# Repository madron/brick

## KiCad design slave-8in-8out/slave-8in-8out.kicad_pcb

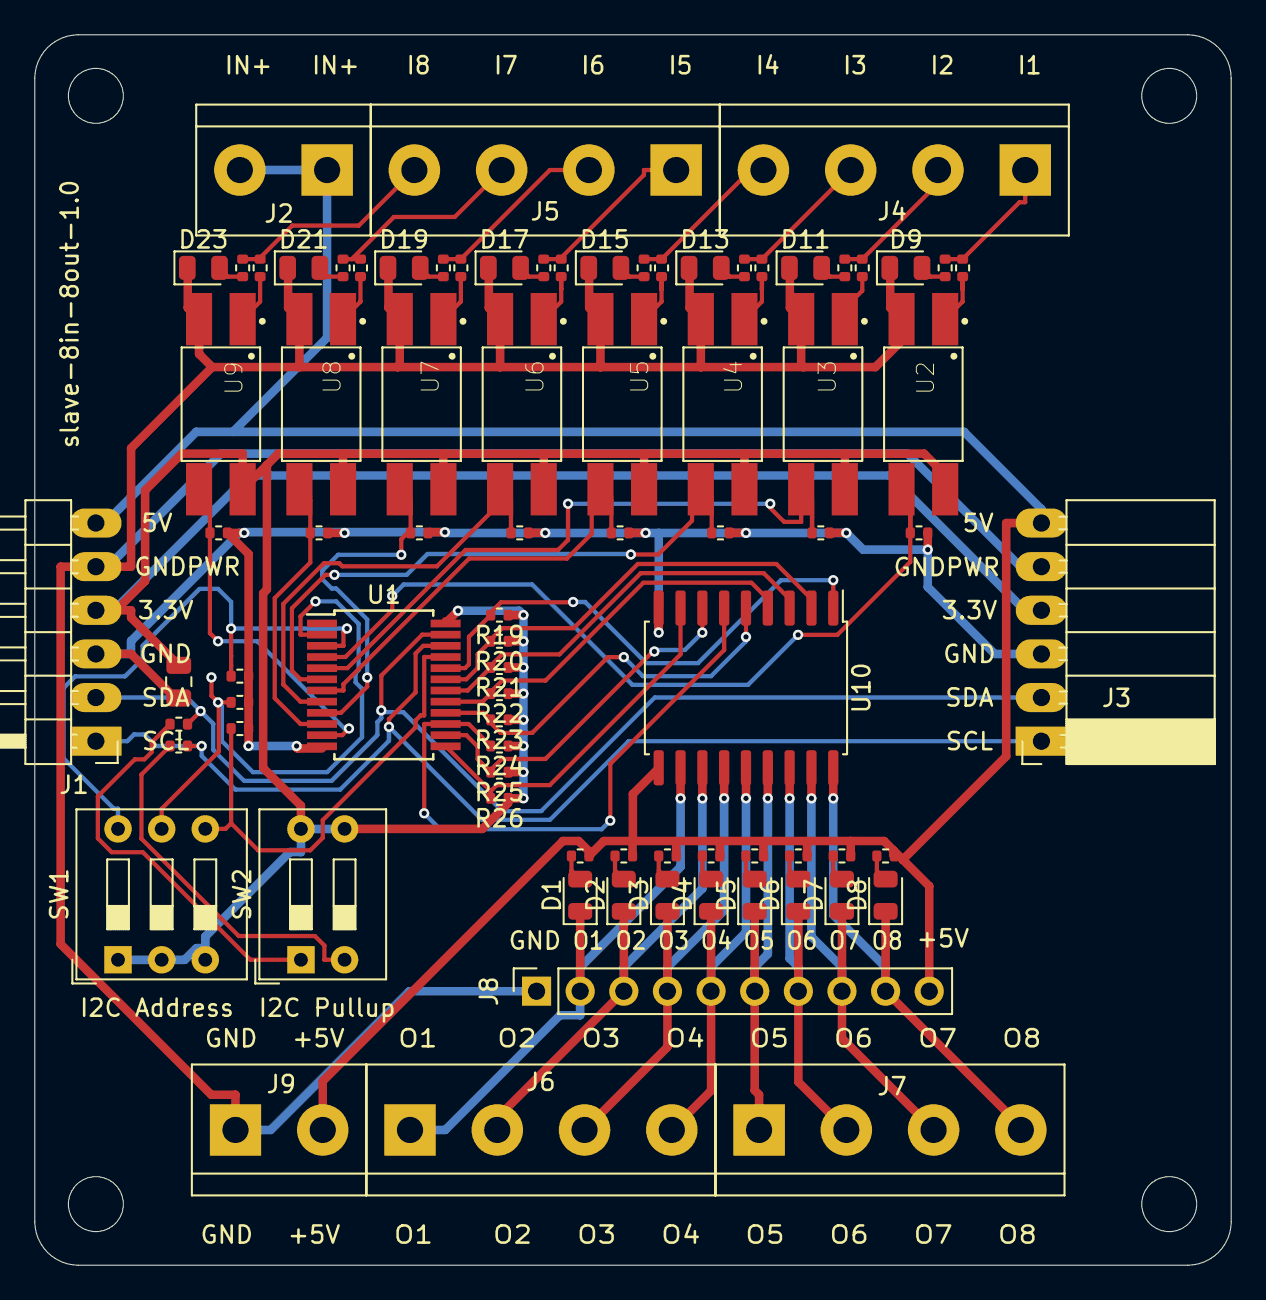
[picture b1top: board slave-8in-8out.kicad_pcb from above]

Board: 2 copper layers, 69.6 x 71.6 mm, 87 parts (0 on the bottom side), 67 nets.

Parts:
C1: 100nF; C_0805_2012Metric
D1, D2, D3, D4, D5, D6, D7, D8, D9, D11, D13, D15, D17, D19, D21, D23: LED; LED_0805_2012Metric
H1, H2, H3, H4: MountingHole; MountingHole_3.2mm_M3
J1: Conn_01x06_Male; PinHeader_1x06_P2.54mm_Horizontal
J2, J9: Screw_Terminal_01x02; TerminalBlock_bornier-2_P5.08mm
J3: Conn_01x06_Female; PinSocket_1x06_P2.54mm_Horizontal
J4, J5, J6, J7: Screw_Terminal_01x04; TerminalBlock_bornier-4_P5.08mm
J8: Conn_01x10_Female; PinSocket_1x10_P2.54mm_Vertical
R1, R2, R5, R8, R19, R20, R21, R22, R23, R24, R25, R26, R28, R29, R30, R31, R34, R37, R40, R43, R46: 10k; R_0402_1005Metric
R3, R4, R6, R7, R9, R10, R11, R12, R13, R14, R15, R16, R17, R18, R32, R33, R35, R36, R38, R39, R41, R42, R44, R45: 680; R_0402_1005Metric
SW1: SW_DIP_x03; SW_DIP_SPSTx03_Slide_9.78x9.8mm_W7.62mm_P2.54mm
SW2: SW_DIP_x02; SW_DIP_SPSTx02_Slide_9.78x7.26mm_W7.62mm_P2.54mm
U1: PCF8575; SSOP-24_5.3x8.2mm_P0.65mm
U2, U3, U4, U5, U6, U7, U8, U9: EL817
U10: ULN2803A; SOIC-18W_7.5x11.6mm_P1.27mm

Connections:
+3V3: C1.1, J1.4, J3.4, R19.1, R20.1, R21.1, R22.1, R23.1, R24.1, R25.1, R26.1, SW1.1, SW1.2, SW1.3, SW2.3, SW2.4, U1.24 (VCC), U2.4, U3.4, U4.4, U5.4, U6.4, U7.4, U8.4, U9.4
+5V: J1.6, J2.1, J2.2, J3.6, J8.10, J9.2, R11.2, R12.2, R13.2, R14.2, R15.2, R16.2, R17.2, R18.2, U10.10 (COM)
A0: R30.1, SW1.4, U1.21 (A0)
A1: R29.1, SW1.5, U1.2 (A1)
A2: R28.1, SW1.6, U1.3 (A2)
GND: C1.2, J1.3, J3.3, R5.1, R8.1, R28.2, R29.2, R30.2, R31.1, R34.1, R37.1, R40.1, R43.1, R46.1, U1.12 (GND), U10.9 (GND)
GNDPWR: D9.1 (K), D11.1 (K), D13.1 (K), D15.1 (K), D17.1 (K), D19.1 (K), D21.1 (K), D23.1 (K), J1.5, J3.5, J8.1, J9.1, U2.2, U3.2, U4.2, U5.2, U6.2, U7.2, U8.2, U9.2
GPA0: R26.2, U1.13 (P10), U10.8 (I8)
GPA1: R25.2, U1.14 (P11), U10.7 (I7)
GPA2: R24.2, U1.15 (P12), U10.6 (I6)
GPA3: R23.2, U1.16 (P13), U10.5 (I5)
GPA4: R22.2, U1.17 (P14), U10.4 (I4)
GPA5: R21.2, U1.18 (P15), U10.3 (I3)
GPA6: R20.2, U1.19 (P16), U10.2 (I2)
GPA7: R19.2, U1.20 (P17), U10.1 (I1)
GPB0: R5.2, U1.4 (P00), U2.3
GPB1: R8.2, U1.5 (P01), U3.3
GPB2: R31.2, U1.6 (P02), U4.3
GPB3: R34.2, U1.7 (P03), U5.3
GPB4: R37.2, U1.8 (P04), U6.3
GPB5: R40.2, U1.9 (P05), U7.3
GPB6: R43.2, U1.10 (P06), U8.3
GPB7: R46.2, U1.11 (P07), U9.3
I1: J4.1, R3.1, R4.2
I2: J4.2, R6.1, R7.2
I3: J4.3, R9.1, R10.2
I4: J4.4, R32.1, R33.2
I5: J5.1, R35.1, R36.2
I6: J5.2, R38.1, R39.2
I7: J5.3, R41.1, R42.2
I8: J5.4, R44.1, R45.2
unnamed: D1.2 (A), R12.1
unnamed: D2.2 (A), R13.1
unnamed: D3.2 (A), R14.1
unnamed: D4.2 (A), R15.1
unnamed: D5.2 (A), R16.1
unnamed: D6.2 (A), R17.1
unnamed: D7.2 (A), R18.1
unnamed: D8.2 (A), R11.1
unnamed: D9.2 (A), R3.2
unnamed: D11.2 (A), R6.2
unnamed: D13.2 (A), R9.2
unnamed: D15.2 (A), R32.2
unnamed: D17.2 (A), R35.2
unnamed: D19.2 (A), R38.2
unnamed: D21.2 (A), R41.2
unnamed: D23.2 (A), R44.2
unnamed: R1.1, SW2.1
unnamed: R2.1, SW2.2
unnamed: R4.1, U2.1
unnamed: R7.1, U3.1
unnamed: R10.1, U4.1
unnamed: R33.1, U5.1
unnamed: R36.1, U6.1
unnamed: R39.1, U7.1
unnamed: R42.1, U8.1
unnamed: R45.1, U9.1
O1: D1.1 (K), J6.1, J8.2, U10.11 (O8)
O2: D2.1 (K), J6.2, J8.3, U10.12 (O7)
O3: D3.1 (K), J6.3, J8.4, U10.13 (O6)
O4: D4.1 (K), J6.4, J8.5, U10.14 (O5)
O5: D5.1 (K), J7.1, J8.6, U10.15 (O4)
O6: D6.1 (K), J7.2, J8.7, U10.16 (O3)
O7: D7.1 (K), J7.3, J8.8, U10.17 (O2)
O8: D8.1 (K), J7.4, J8.9, U10.18 (O1)
SCL: J1.1, J3.1, R2.2, U1.22 (SCL)
SDA: J1.2, J3.2, R1.2, U1.23 (SDA)

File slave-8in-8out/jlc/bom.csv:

Comment,Designator,Footprint,LCSC Part #
100nF Unpolarized capacitor,C1,C_0805_2012Metric,C49678
LED Light emitting diode,"D1,D2,D3,D4,D5,D6,D7,D8,D9,D11,D13,D15,D17,D19,D21,D23",LED_0805_2012Metric,C84256
10k Resistor,"R1,R2,R5,R8,R19,R20,R21,R22,R23,R24,R25,R26,R28,R29,R30,R31,R34,R37,R40,R43,R46",R_0402_1005Metric,C25744
680 Resistor,"R3,R4,R6,R7,R9,R10,R11,R12,R13,R14,R15,R16,R17,R18,R32,R33,R35,R36,R38,R39,R41,R42,R44,R45",R_0402_1005Metric,C25130
PCF8575 ,U1,SSOP-24_5.3x8.2mm_P0.65mm,C12251
"EL817 DC Optocoupler, Vce 35V, CTR 50-300%, DIP-4","U2,U3,U4,U5,U6,U7,U8,U9",EL817,C106900
"ULN2803A Darlington Transistor Arrays, SOIC18/DIP18",U10,SOIC-18W_7.5x11.6mm_P1.27mm,C9683

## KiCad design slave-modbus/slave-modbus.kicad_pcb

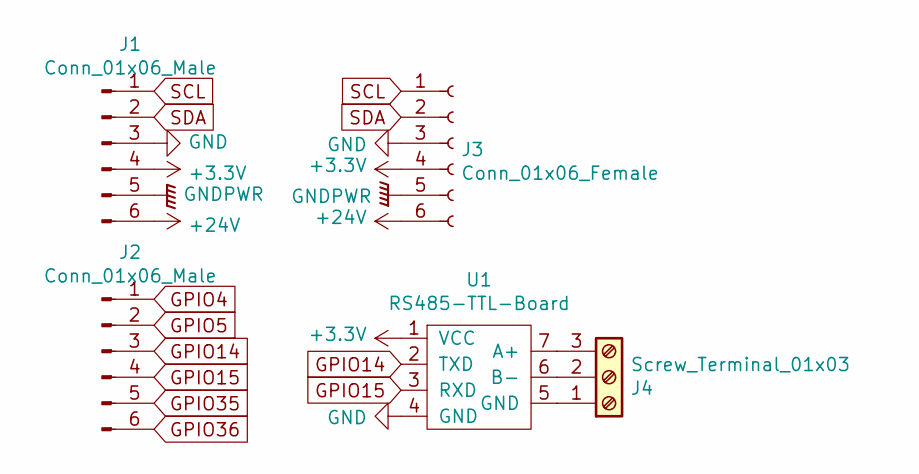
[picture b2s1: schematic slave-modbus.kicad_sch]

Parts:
J1, J2: Conn_01x06_Male; PinHeader_1x06_P2.54mm_Horizontal
J3: Conn_01x06_Female; PinSocket_1x06_P2.54mm_Horizontal
J4: Screw_Terminal_01x03; TerminalBlock_Phoenix_PT-1,5-3-3.5-H_1x03_P3.50mm_Horizontal
U1: RS485-TTL-Board; RS485-TTL-Board-DsdTech

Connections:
+3V3: J1.4, J3.4, U1.1 (VCC)
+24V: J1.6, J3.6
GND: J1.3, J3.3, U1.4 (GND)
GNDPWR: J1.5, J3.5
GPIO4: J2.1
GPIO5: J2.2
GPIO14: J2.3, U1.2 (TXD)
GPIO15: J2.4, U1.3 (RXD)
GPIO35: J2.5
GPIO36: J2.6
unnamed: J4.1, U1.5 (GND)
unnamed: J4.2, U1.6 (B-)
unnamed: J4.3, U1.7 (A+)
SCL: J1.1, J3.1
SDA: J1.2, J3.2

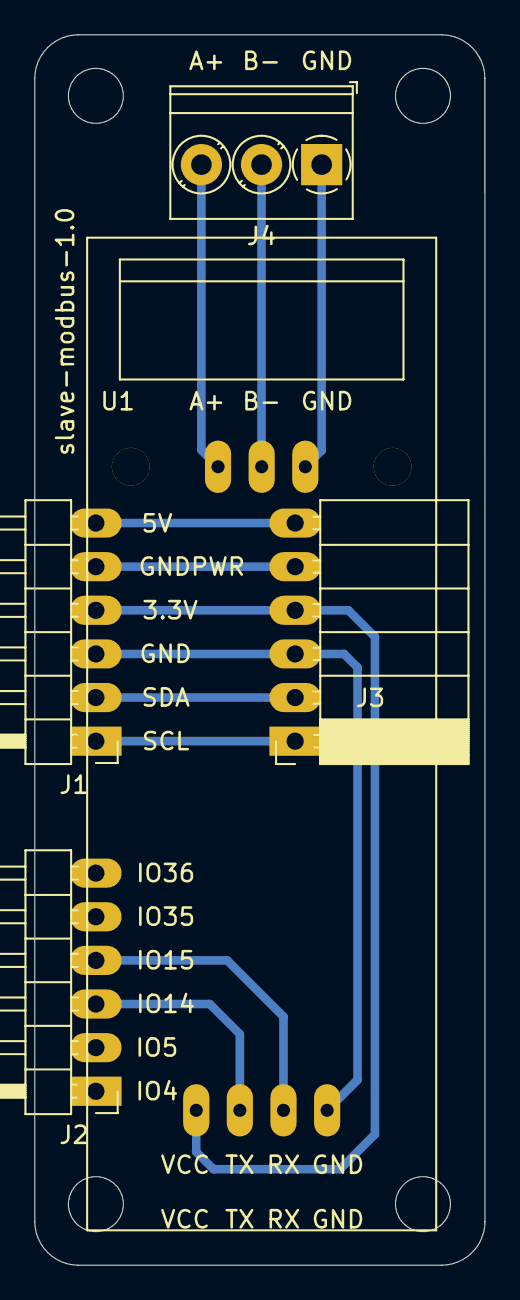
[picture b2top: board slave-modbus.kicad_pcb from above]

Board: 2 copper layers, 26.2 x 71.6 mm, 9 parts (0 on the bottom side), 11 nets.

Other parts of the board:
H1, H2, H3, H4: MountingHole; MountingHole_3.2mm_M3

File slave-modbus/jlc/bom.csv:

Comment,Designator,Footprint,LCSC Part #
"Conn_01x06_Male Generic connector, single row, 01x06, script generated (kicad-library-utils/schlib/autogen/connector/)","J1,J2",PinHeader_1x06_P2.54mm_Horizontal,
"Conn_01x06_Female Generic connector, single row, 01x06, script generated (kicad-library-utils/schlib/autogen/connector/)",J3,PinSocket_1x06_P2.54mm_Horizontal,
"Screw_Terminal_01x03 Generic screw terminal, single row, 01x03, script generated (kicad-library-utils/schlib/autogen/connector/)",J4,"TerminalBlock_Phoenix_PT-1,5-3-3.5-H_1x03_P3.50mm_Horizontal",
RS485-TTL-Board ,U1,RS485-TTL-Board-DsdTech,

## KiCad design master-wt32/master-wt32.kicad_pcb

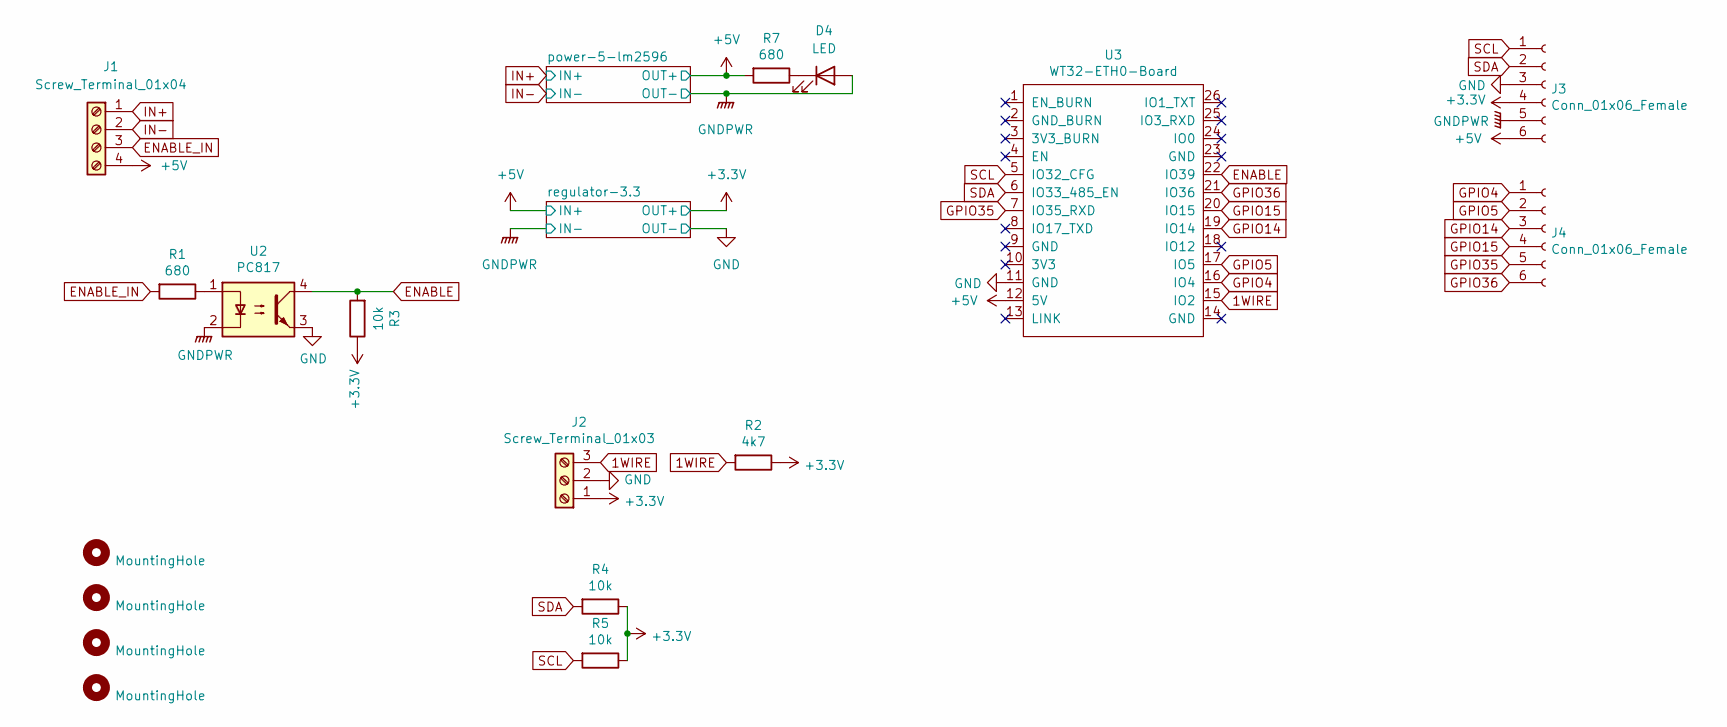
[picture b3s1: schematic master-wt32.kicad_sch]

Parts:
D4: LED; LED_D5.0mm
H1, H2, H3, H4: MountingHole; MountingHole_3.2mm_M3
J1: Screw_Terminal_01x04; TerminalBlock_bornier-4_P5.08mm
J2: Screw_Terminal_01x03; TerminalBlock_bornier-3_P5.08mm
J3, J4: Conn_01x06_Female; PinSocket_1x06_P2.54mm_Horizontal
R1, R7: 680; R_Axial_DIN0207_L6.3mm_D2.5mm_P7.62mm_Horizontal
R2: 4k7; R_Axial_DIN0207_L6.3mm_D2.5mm_P7.62mm_Horizontal
R3: 10k; R_Axial_DIN0207_L6.3mm_D2.5mm_P7.62mm_Horizontal
R4, R5: 10k; R_Axial_DIN0207_L6.3mm_D2.5mm_P7.62mm_Horizontal; LCSC C25744
U2: PC817; DIP-4_W7.62mm
U3: WT32-ETH0-Board; WT32-ETH01-Board-Reversed

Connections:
1WIRE: J2.3, R2.2, U3.15 (IO2)
+3V3: J2.1, J3.4, R2.1, R3.1, R4.1, R5.1; also elsewhere on the board
+5V: J1.4, J3.6, R7.2, U3.12 (5V); also elsewhere on the board
ENABLE: R3.2, U2.4, U3.22 (IO39)
ENABLE_IN: J1.3, R1.2
GNDPWR: D4.2 (A), J2.2, J3.3, J3.5, U2.2, U2.3, U3.11 (GND); also elsewhere on the board
GPIO4: J4.1, U3.16 (IO4)
GPIO5: J4.2, U3.17 (IO5)
GPIO14: J4.3, U3.19 (IO14)
GPIO15: J4.4, U3.20 (IO15)
GPIO35: J4.5, U3.7 (IO35_RXD)
GPIO36: J4.6, U3.21 (IO36)
IN+: J1.1; also elsewhere on the board
IN-: J1.2; also elsewhere on the board
unnamed: D4.1 (K), R7.1
unnamed: R1.1, U2.1
SCL: J3.1, R5.2, U3.5 (IO32_CFG)
SDA: J3.2, R4.2, U3.6 (IO33_485_EN)

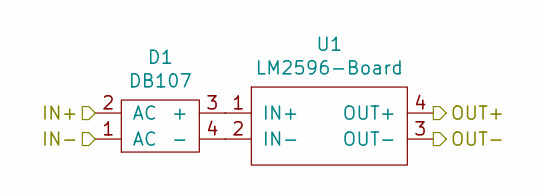
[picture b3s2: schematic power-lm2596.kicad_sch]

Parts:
D1: DB107
U1: LM2596-Board

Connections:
+5V: U1.4 (OUT+); also elsewhere on the board
GNDPWR: U1.3 (OUT-); also elsewhere on the board
IN+: D1.2 (AC); also elsewhere on the board
IN-: D1.1 (AC); also elsewhere on the board
unnamed: D1.3 (+), U1.1 (IN+)
unnamed: D1.4 (-), U1.2 (IN-)

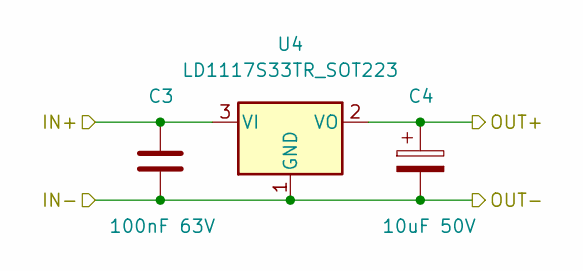
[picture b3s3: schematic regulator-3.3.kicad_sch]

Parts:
C3: 100nF 63V; C_Rect_L7.0mm_W2.0mm_P5.00mm
C4: 10uF 50V; CP_Radial_D5.0mm_P2.50mm
U4: LD1117S33TR_SOT223; TO-220-3_Vertical

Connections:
+3V3: C4.1, U4.2 (VO); also elsewhere on the board
+5V: C3.1, U4.3 (VI); also elsewhere on the board
GNDPWR: C3.2, C4.2, U4.1 (GND); also elsewhere on the board

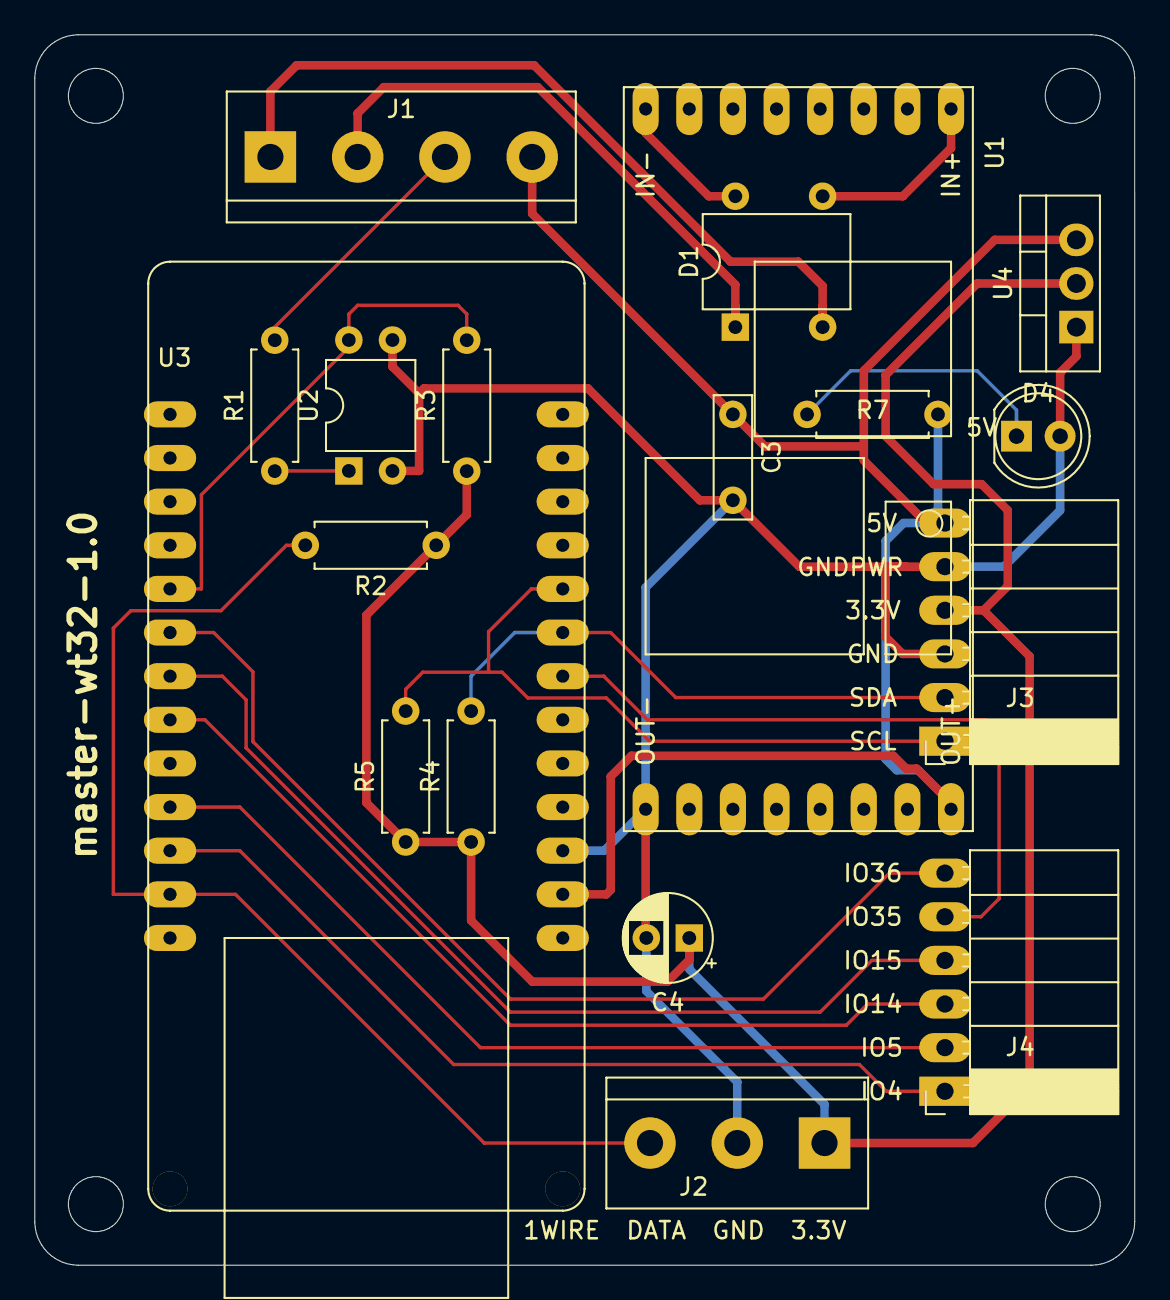
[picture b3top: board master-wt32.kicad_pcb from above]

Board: 2 copper layers, 64.0 x 71.6 mm, 22 parts (0 on the bottom side), 20 nets.

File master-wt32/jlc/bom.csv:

Comment,Designator,Footprint,LCSC Part #
100nF 63V Unpolarized capacitor,C3,C_Rect_L7.0mm_W2.0mm_P5.00mm,
10uF 50V Polarized capacitor,C4,CP_Radial_D5.0mm_P2.50mm,
DB107 ,D1,DB107,
LED Light emitting diode,D4,LED_D5.0mm,
MountingHole Mounting Hole without connection,"H1,H2,H3,H4",MountingHole_3.2mm_M3,
"Screw_Terminal_01x04 Generic screw terminal, single row, 01x04, script generated (kicad-library-utils/schlib/autogen/connector/)",J1,TerminalBlock_bornier-4_P5.08mm,
"Screw_Terminal_01x03 Generic screw terminal, single row, 01x03, script generated (kicad-library-utils/schlib/autogen/connector/)",J2,TerminalBlock_bornier-3_P5.08mm,
"Conn_01x06_Female Generic connector, single row, 01x06, script generated (kicad-library-utils/schlib/autogen/connector/)","J3,J4",PinSocket_1x06_P2.54mm_Horizontal,
680 Resistor,"R1,R7",R_Axial_DIN0207_L6.3mm_D2.5mm_P7.62mm_Horizontal,
4k7 Resistor,R2,R_Axial_DIN0207_L6.3mm_D2.5mm_P7.62mm_Horizontal,
10k Resistor,"R3,R4,R5",R_Axial_DIN0207_L6.3mm_D2.5mm_P7.62mm_Horizontal,C25744
LM2596-Board ,U1,LM2596-Board,
"PC817 DC Optocoupler, Vce 35V, CTR 50-300%, DIP-4",U2,DIP-4_W7.62mm,
WT32-ETH0-Board ,U3,WT32-ETH01-Board-Reversed,
"LD1117S33TR_SOT223 800mA Fixed Low Drop Positive Voltage Regulator, Fixed Output 3.3V, SOT-223",U4,TO-220-3_Vertical,

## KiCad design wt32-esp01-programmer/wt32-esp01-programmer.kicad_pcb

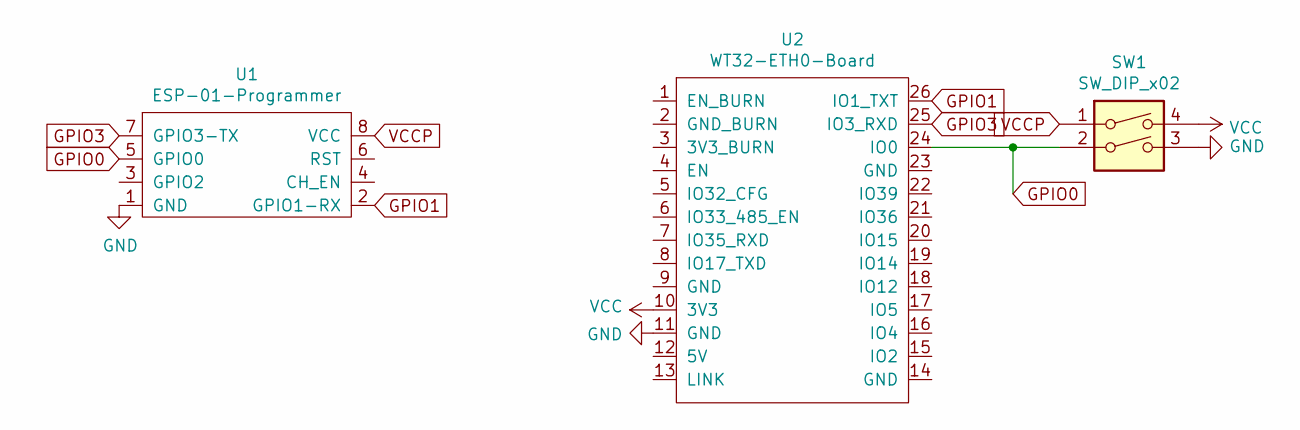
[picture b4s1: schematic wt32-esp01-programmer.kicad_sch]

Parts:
SW1: SW_DIP_x02; SW_DIP_SPSTx02_Slide_9.78x7.26mm_W7.62mm_P2.54mm
U1: ESP-01-Programmer
U2: WT32-ETH0-Board; WT32-ETH01-Board-Reversed

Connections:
GND: SW1.3, U1.1 (GND), U2.11 (GND)
GPIO0: SW1.2, U1.5 (GPIO0), U2.24 (IO0)
GPIO1: U1.2 (GPIO1-RX), U2.26 (IO1_TXT)
GPIO3: U1.7 (GPIO3-TX), U2.25 (IO3_RXD)
VCC: SW1.4, U2.10 (3V3)
VCCP: SW1.1, U1.8 (VCC)

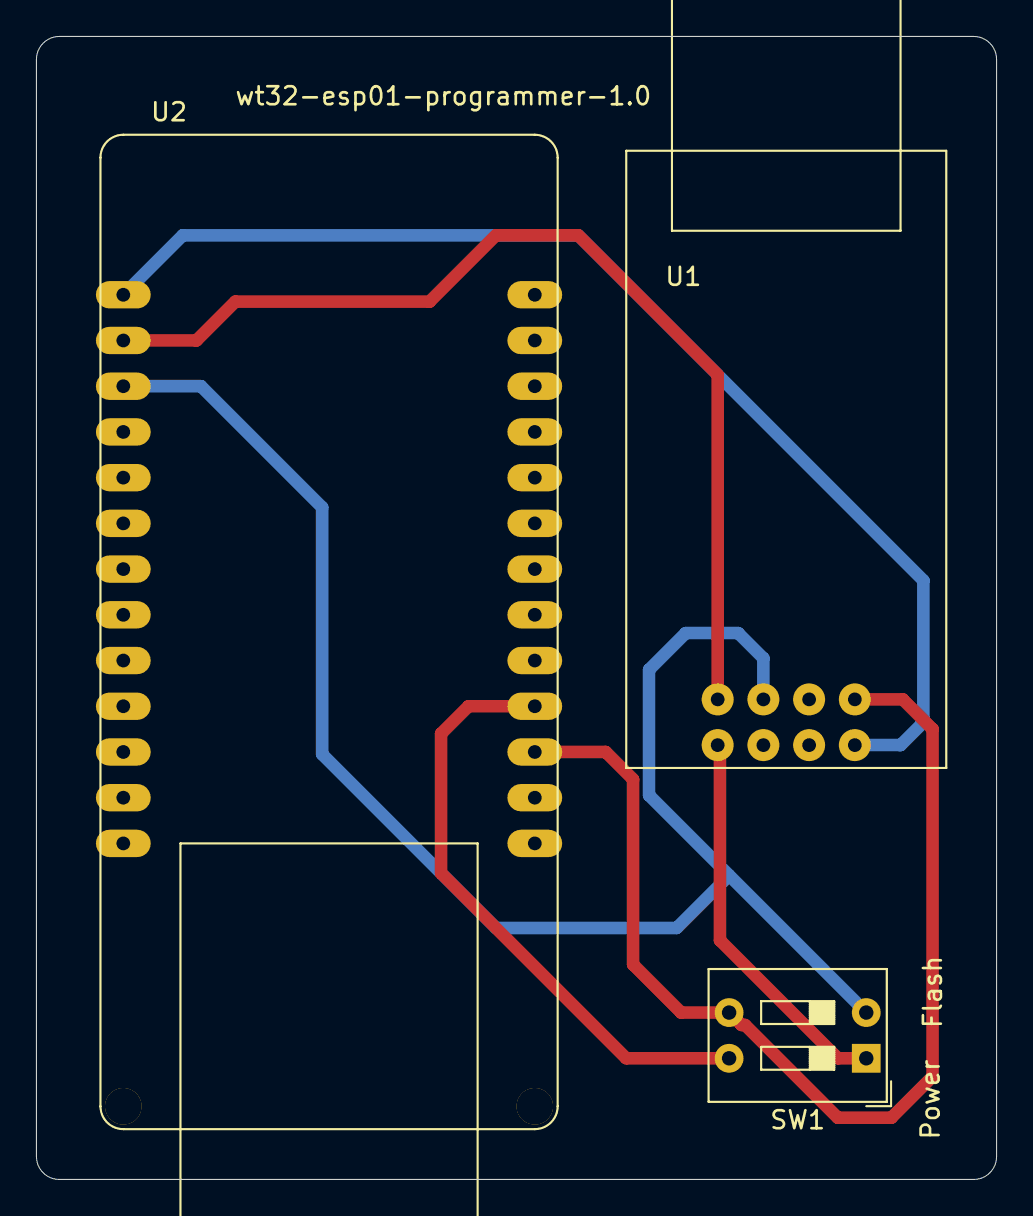
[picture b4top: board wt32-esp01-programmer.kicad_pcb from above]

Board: 2 copper layers, 53.3 x 63.5 mm, 3 parts (0 on the bottom side), 6 nets.

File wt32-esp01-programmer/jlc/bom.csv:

Comment,Designator,Footprint,LCSC Part #
"SW_DIP_x02 2x DIP Switch, Single Pole Single Throw (SPST) switch, small symbol",SW1,SW_DIP_SPSTx02_Slide_9.78x7.26mm_W7.62mm_P2.54mm,
ESP-01-Programmer ,U1,ESP-01-Programmer,
WT32-ETH0-Board ,U2,WT32-ETH01-Board-Reversed,

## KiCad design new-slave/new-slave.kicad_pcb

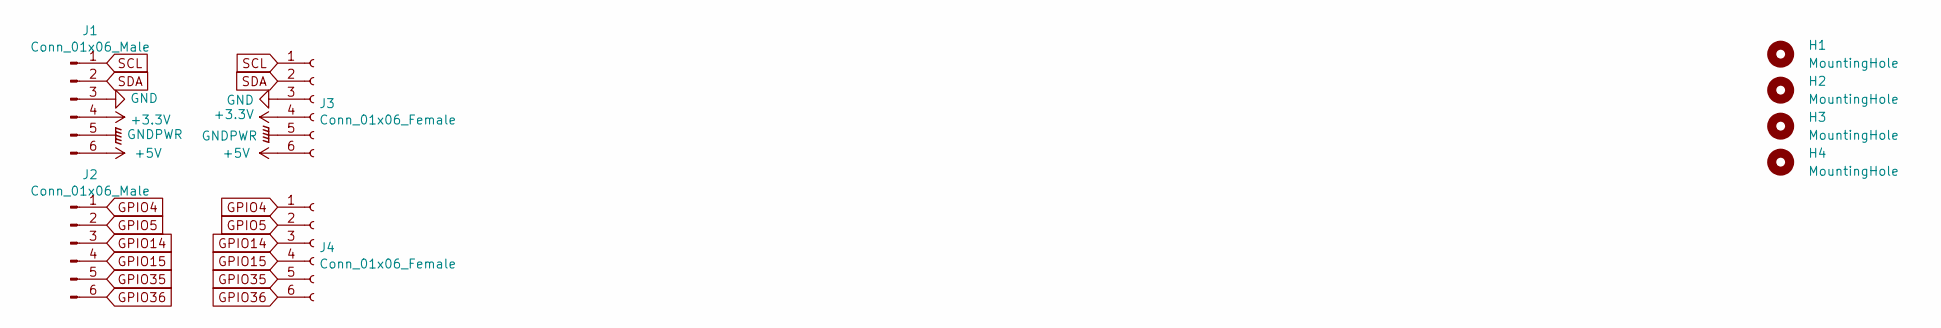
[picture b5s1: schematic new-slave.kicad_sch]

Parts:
H1, H2, H3, H4: MountingHole; MountingHole_3.2mm_M3
J1, J2: Conn_01x06_Male; PinHeader_1x06_P2.54mm_Horizontal
J3, J4: Conn_01x06_Female; PinSocket_1x06_P2.54mm_Horizontal

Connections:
+3V3: J1.4, J3.4
+5V: J1.6, J3.6
GND: J1.3, J3.3
GNDPWR: J1.5, J3.5
GPIO4: J2.1, J4.1
GPIO5: J2.2, J4.2
GPIO14: J2.3, J4.3
GPIO15: J2.4, J4.4
GPIO35: J2.5, J4.5
GPIO36: J2.6, J4.6
SCL: J1.1, J3.1
SDA: J1.2, J3.2

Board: 2 copper layers, 8 parts (0 on the bottom side), 12 nets, no tracks yet.

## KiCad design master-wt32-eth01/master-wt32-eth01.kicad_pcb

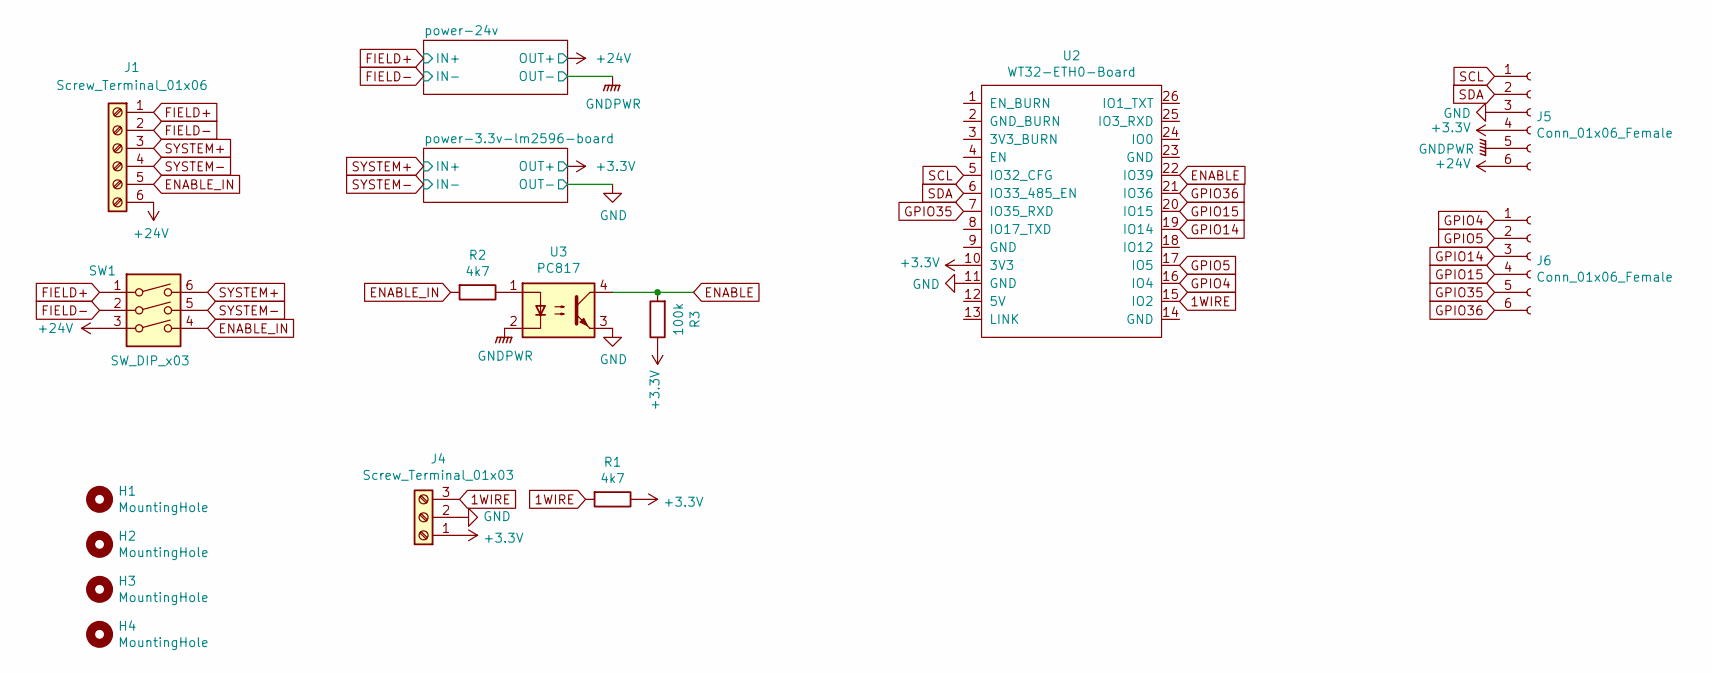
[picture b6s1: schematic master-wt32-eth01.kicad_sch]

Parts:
H1, H2, H3, H4: MountingHole; MountingHole_3.2mm_M3
J1: Screw_Terminal_01x06; TerminalBlock_bornier-6_P5.08mm
J4: Screw_Terminal_01x03; TerminalBlock_bornier-3_P5.08mm
J5, J6: Conn_01x06_Female; PinSocket_1x06_P2.54mm_Horizontal
R1, R2: 4k7; R_Axial_DIN0207_L6.3mm_D2.5mm_P7.62mm_Horizontal
R3: 100k; R_Axial_DIN0207_L6.3mm_D2.5mm_P7.62mm_Horizontal
SW1: SW_DIP_x03; SW_DIP_SPSTx03_Slide_9.78x9.8mm_W7.62mm_P2.54mm
U2: WT32-ETH0-Board; WT32-ETH01-Board-Reversed
U3: PC817; DIP-4_W7.62mm

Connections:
1WIRE: J4.3, R1.2, U2.15 (IO2)
+3V3: J4.1, J5.4, R1.1, R3.1, U2.10 (3V3); also elsewhere on the board
+24V: J1.6, J5.6, SW1.3; also elsewhere on the board
ENABLE: R3.2, U2.22 (IO39), U3.4
ENABLE_IN: J1.5, R2.2, SW1.4
FIELD+: J1.1, SW1.1; also elsewhere on the board
FIELD-: J1.2, SW1.2; also elsewhere on the board
GND: J4.2, J5.3, U2.11 (GND), U3.3; also elsewhere on the board
GNDPWR: J5.5, U3.2; also elsewhere on the board
GPIO4: J6.1, U2.16 (IO4)
GPIO5: J6.2, U2.17 (IO5)
GPIO14: J6.3, U2.19 (IO14)
GPIO15: J6.4, U2.20 (IO15)
GPIO35: J6.5, U2.7 (IO35_RXD)
GPIO36: J6.6, U2.21 (IO36)
unnamed: R2.1, U3.1
SCL: J5.1, U2.5 (IO32_CFG)
SDA: J5.2, U2.6 (IO33_485_EN)
SYSTEM+: J1.3, SW1.6; also elsewhere on the board
SYSTEM-: J1.4, SW1.5; also elsewhere on the board

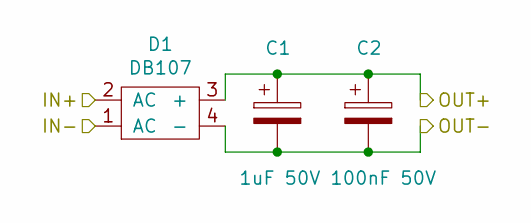
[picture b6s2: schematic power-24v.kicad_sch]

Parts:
C1: 1uF 50V; CP_Radial_D5.0mm_P2.50mm
C2: 100nF 50V; C_Rect_L7.0mm_W2.0mm_P5.00mm
D1: DB107

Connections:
+24V: C1.1, C2.1, D1.3 (+); also elsewhere on the board
FIELD+: D1.2 (AC); also elsewhere on the board
FIELD-: D1.1 (AC); also elsewhere on the board
GNDPWR: C1.2, C2.2, D1.4 (-); also elsewhere on the board

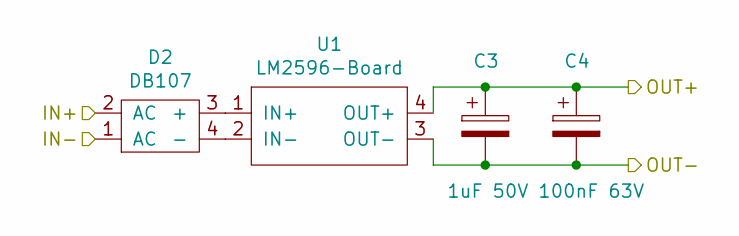
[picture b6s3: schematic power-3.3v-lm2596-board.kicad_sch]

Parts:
C3: 1uF 50V; CP_Radial_D5.0mm_P2.50mm
C4: 100nF 63V; C_Rect_L7.0mm_W2.0mm_P5.00mm
D2: DB107
U1: LM2596-Board

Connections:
+3V3: C3.1, C4.1, U1.4 (OUT+); also elsewhere on the board
GND: C3.2, C4.2, U1.3 (OUT-); also elsewhere on the board
unnamed: D2.3 (+), U1.1 (IN+)
unnamed: D2.4 (-), U1.2 (IN-)
SYSTEM+: D2.2 (AC); also elsewhere on the board
SYSTEM-: D2.1 (AC); also elsewhere on the board

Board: 2 copper layers, 21 parts (0 on the bottom side), 22 nets, no tracks yet.

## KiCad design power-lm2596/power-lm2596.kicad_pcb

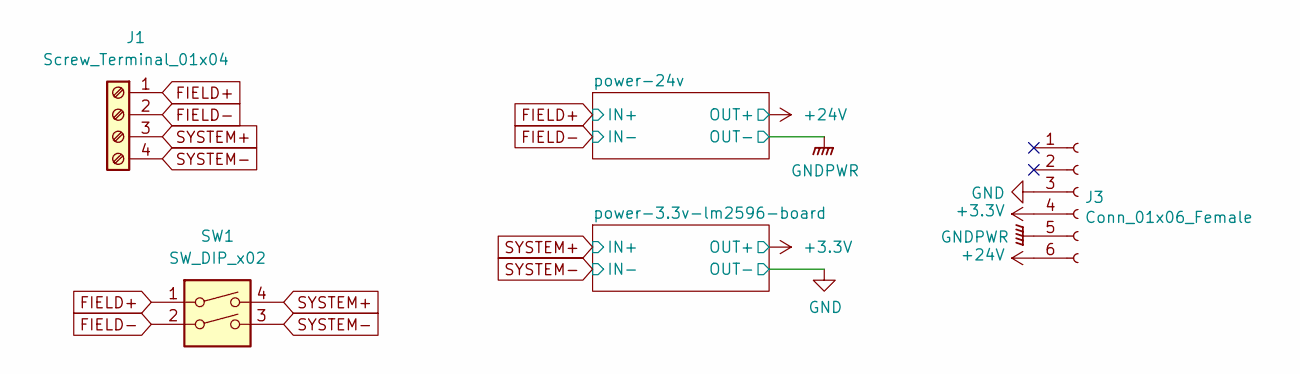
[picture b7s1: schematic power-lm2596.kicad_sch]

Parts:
J1: Screw_Terminal_01x04; TerminalBlock_bornier-4_P5.08mm
J3: Conn_01x06_Female; PinSocket_1x06_P2.54mm_Horizontal
SW1: SW_DIP_x02; SW_DIP_SPSTx02_Slide_9.78x7.26mm_W7.62mm_P2.54mm

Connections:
+3V3: J3.4; also elsewhere on the board
+24V: J3.6; also elsewhere on the board
FIELD+: J1.1, SW1.1; also elsewhere on the board
FIELD-: J1.2, SW1.2; also elsewhere on the board
GND: J3.3; also elsewhere on the board
GNDPWR: J3.5; also elsewhere on the board
SYSTEM+: J1.3, SW1.4; also elsewhere on the board
SYSTEM-: J1.4, SW1.3; also elsewhere on the board

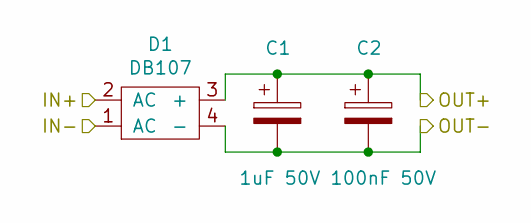
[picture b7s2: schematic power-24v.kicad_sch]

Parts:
C1: 1uF 50V; CP_Radial_D5.0mm_P2.50mm
C2: 100nF 50V; C_Rect_L7.0mm_W2.0mm_P5.00mm
D1: DB107

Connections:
+24V: C1.1, C2.1, D1.3 (+); also elsewhere on the board
FIELD+: D1.2 (AC); also elsewhere on the board
FIELD-: D1.1 (AC); also elsewhere on the board
GNDPWR: C1.2, C2.2, D1.4 (-); also elsewhere on the board

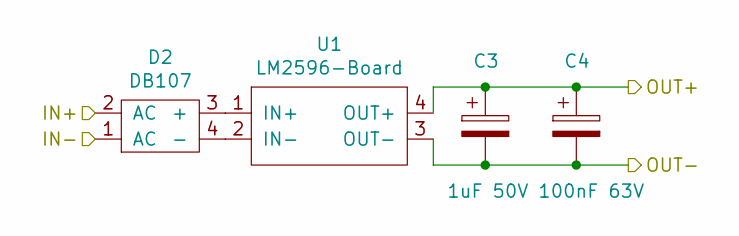
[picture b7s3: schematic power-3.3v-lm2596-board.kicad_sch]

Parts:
C3: 1uF 50V; CP_Radial_D5.0mm_P2.50mm
C4: 100nF 63V; C_Rect_L7.0mm_W2.0mm_P5.00mm
D2: DB107
U1: LM2596-Board

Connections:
+3V3: C3.1, C4.1, U1.4 (OUT+); also elsewhere on the board
GND: C3.2, C4.2, U1.3 (OUT-); also elsewhere on the board
unnamed: D2.3 (+), U1.1 (IN+)
unnamed: D2.4 (-), U1.2 (IN-)
SYSTEM+: D2.2 (AC); also elsewhere on the board
SYSTEM-: D2.1 (AC); also elsewhere on the board

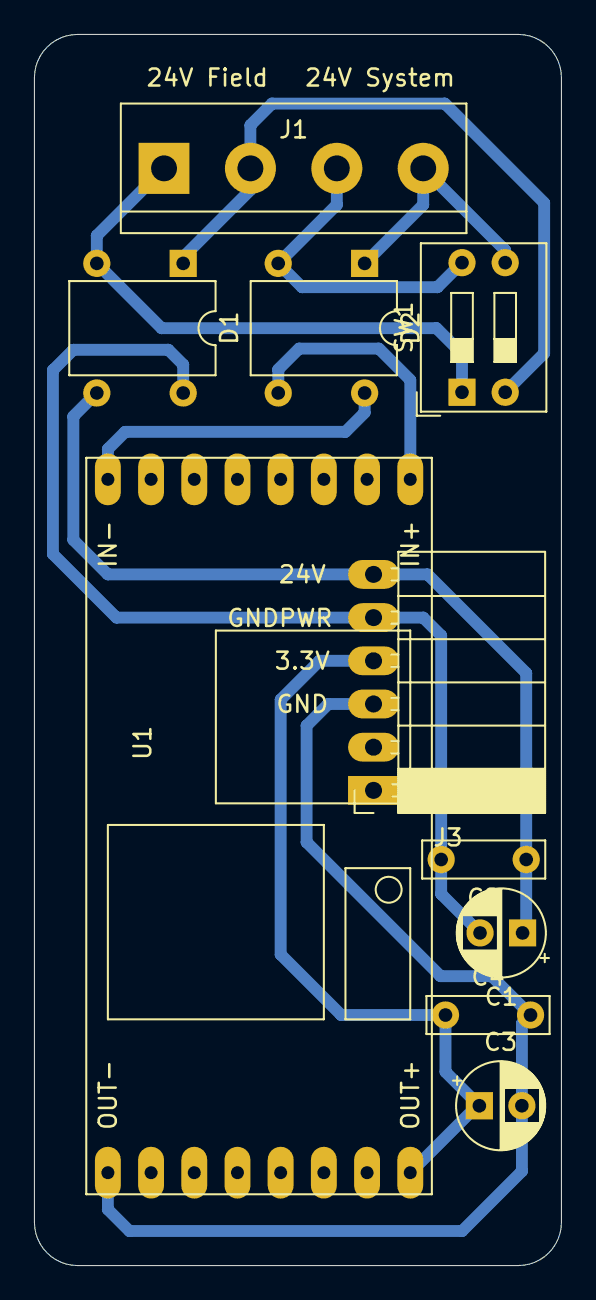
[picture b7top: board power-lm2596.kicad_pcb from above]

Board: 2 copper layers, 31.0 x 72.4 mm, 10 parts (0 on the bottom side), 10 nets.

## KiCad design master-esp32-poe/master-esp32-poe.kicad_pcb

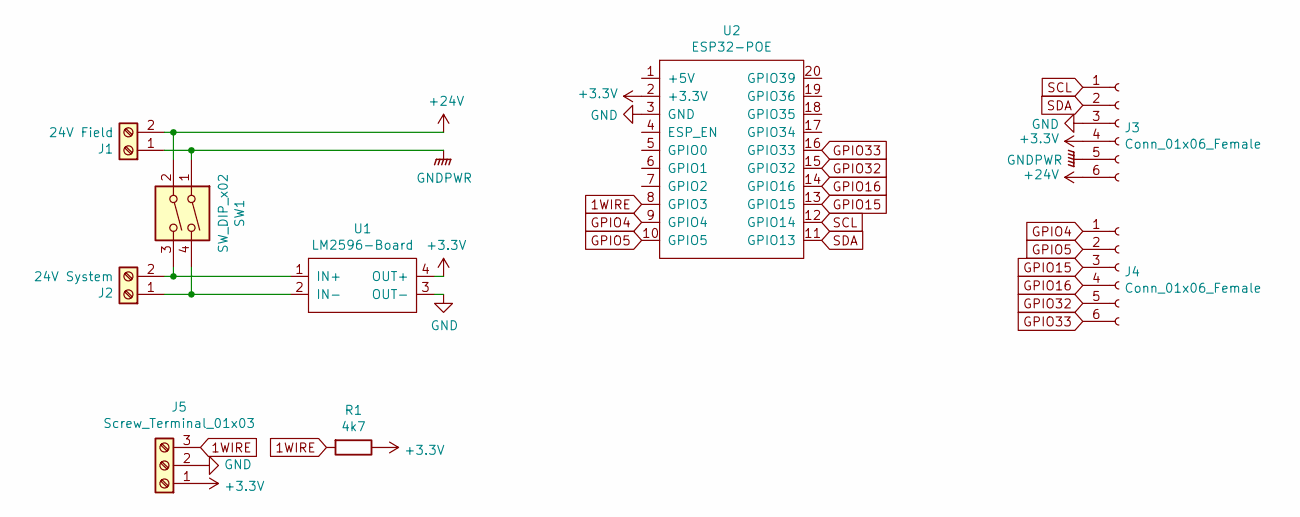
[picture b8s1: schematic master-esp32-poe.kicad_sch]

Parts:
J1: 24V Field; TerminalBlock_bornier-2_P5.08mm
J2: 24V System; TerminalBlock_bornier-2_P5.08mm
J3, J4: Conn_01x06_Female; PinSocket_1x06_P2.54mm_Horizontal
J5: Screw_Terminal_01x03; TerminalBlock_bornier-3_P5.08mm
R1: 4k7; R_Axial_DIN0207_L6.3mm_D2.5mm_P7.62mm_Horizontal
SW1: SW_DIP_x02; SW_DIP_SPSTx02_Slide_9.78x7.26mm_W7.62mm_P2.54mm
U1: LM2596-Board
U2: ESP32-POE

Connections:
1WIRE: J5.3, R1.2, U2.8 (GPIO3)
+3V3: J3.4, J5.1, R1.1, U1.4 (OUT+), U2.2 (+3.3V)
+24V: J1.2, J3.6, SW1.2
GND: J3.3, J5.2, U1.3 (OUT-), U2.3 (GND)
GNDPWR: J1.1, J3.5, SW1.1
GPIO4: J4.1, U2.9 (GPIO4)
GPIO5: J4.2, U2.10 (GPIO5)
GPIO15: J4.3, U2.13 (GPIO15)
GPIO16: J4.4, U2.14 (GPIO16)
GPIO32: J4.5, U2.15 (GPIO32)
GPIO33: J4.6, U2.16 (GPIO33)
unnamed: J2.1, SW1.4, U1.2 (IN-)
unnamed: J2.2, SW1.3, U1.1 (IN+)
SCL: J3.1, U2.12 (GPIO14)
SDA: J3.2, U2.11 (GPIO13)

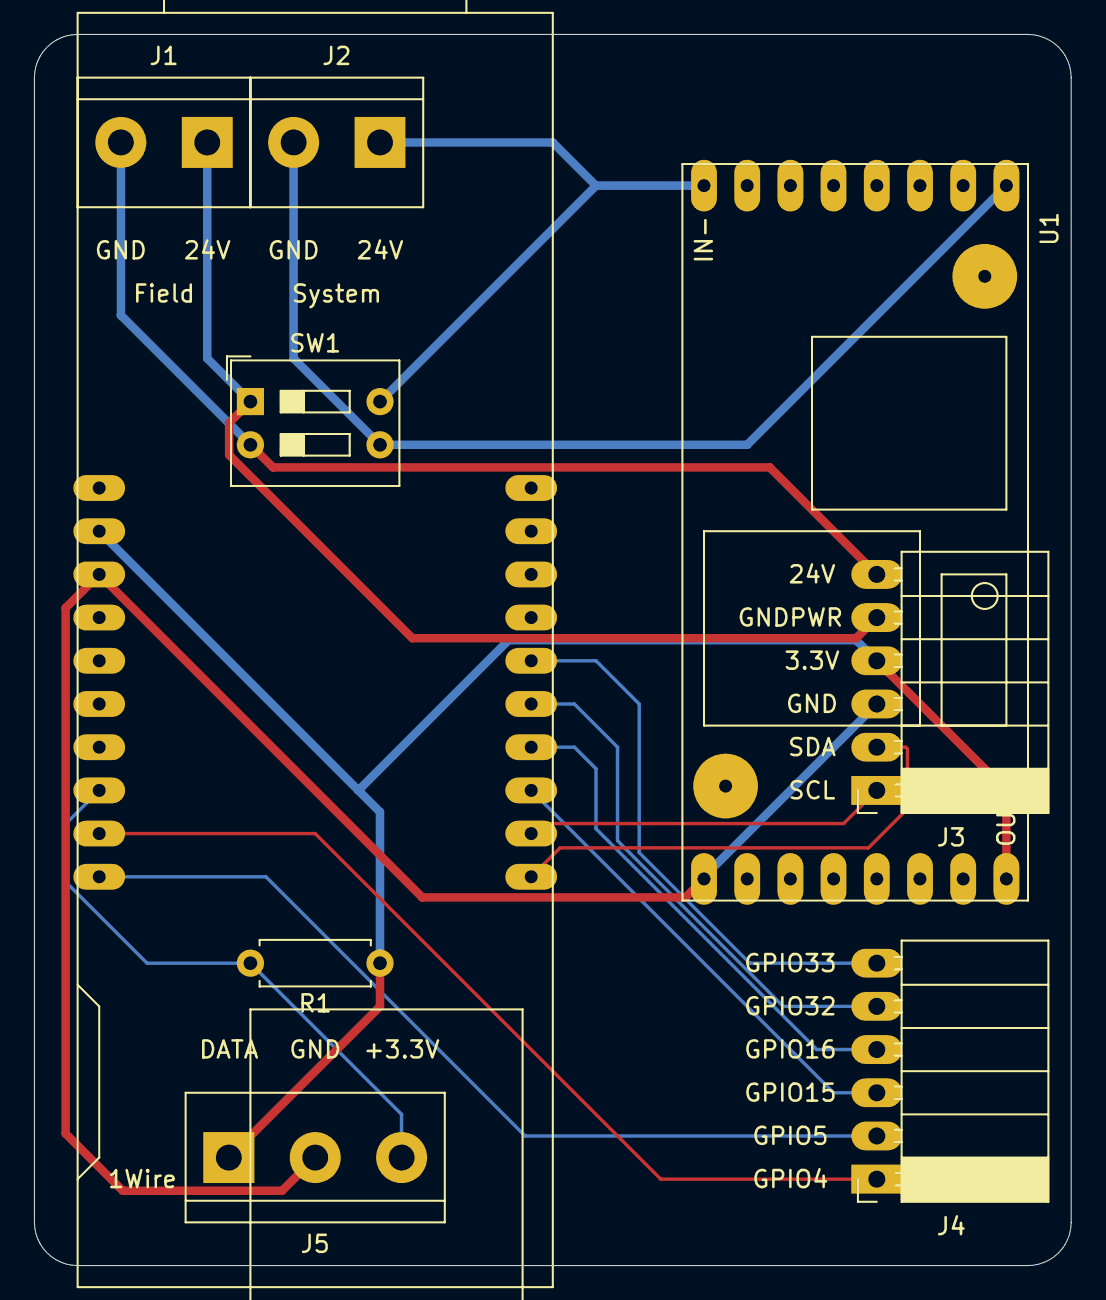
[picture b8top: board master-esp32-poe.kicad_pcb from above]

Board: 2 copper layers, 61.0 x 72.4 mm, 9 parts (0 on the bottom side), 15 nets.
